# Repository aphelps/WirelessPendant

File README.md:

# WirelessPendant
Wireless Pendants

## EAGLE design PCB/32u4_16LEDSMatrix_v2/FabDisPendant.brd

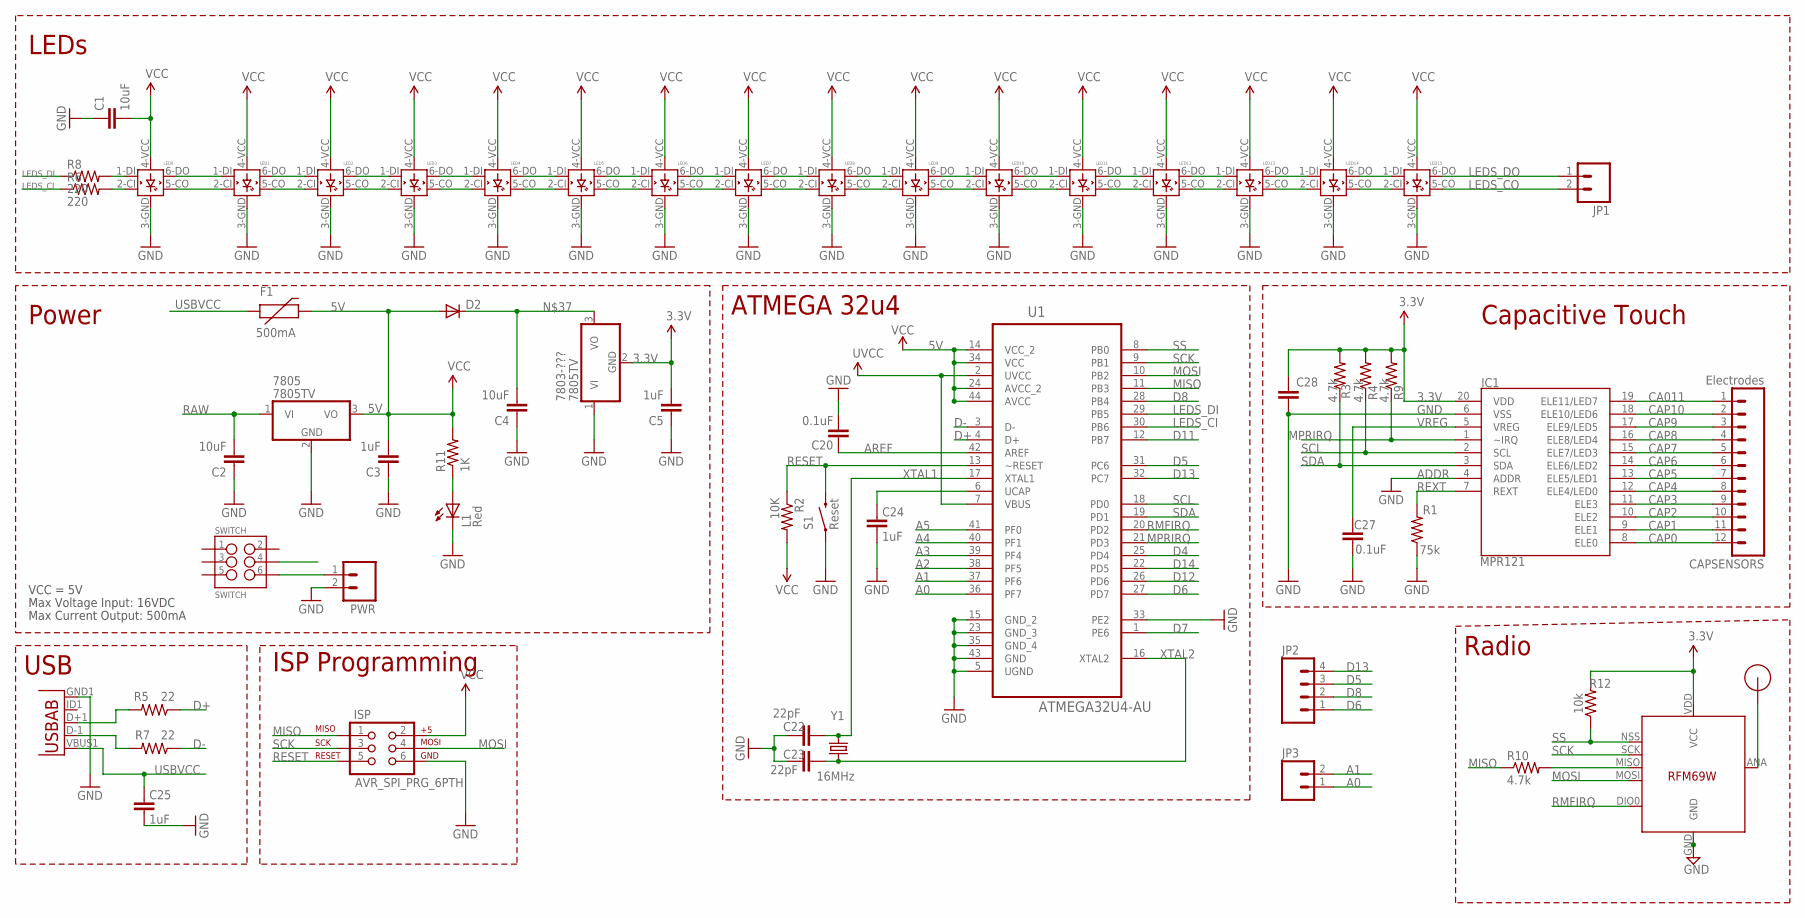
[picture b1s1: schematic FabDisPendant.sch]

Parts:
7803-???, 7805: 7805TV; TO220V
C1, C2, C4: 10uF; 1206
C3, C5: 1uF; 1206
C20, C27, C28: 0.1uF; 0603-CAP
C22, C23: 22pF; 0603-CAP
C24, C25: 1uF; 0603-CAP
CAPSENSORS: Electrodes; 1X12
D2: DIODESOD; SOD-323
F1: 500mA; PTC-1206
IC1: MPR121; QFN-20-0.4MM-V2
ISP: AVR_SPI_PRG_6PTH; 2X3
JP1, JP3: M02PTH; 1X02
JP2: M04PTH; 1X04
L1: Red; LED-0603
LED0, LED1, LED2, LED3, LED4, LED5, LED6, LED7, LED8, LED9, LED10, LED11, LED12, LED13, LED14, LED15: APA102; 5050
PWR: M025MM; SCREWTERMINAL-5MM-2
R1: 75k; 0603-RES
R2: 10K; 0603-RES
R3, R4, R9, R10: 4.7k; 0603-RES
R5, R7: 22; 0603-RES
R6, R8: 220; 0603-RES@1
R11: 1K; 0603-RES
R12: 10k; 0603-RES
RMF69: RFM69; RFM69W-MINPADS
S1: Reset; TACTILE_SWITCH_SMD
SWITCH: SWITCH; 2X3
U1: ATMEGA32U4-AU; QFP80P1200X1200X120-44N
U$1: RFM12B_ANTENNA; RFM12B-ANTENNA
X2: USB-ABIN&OUT; USB-AB-MICRO-SMD-V03-IN&OUT
Y1: 16MHz; CRYSTAL-SMD-5X3

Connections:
3.3V: 7803-???.2 (GND), C5.2, C28.1, IC1.20 (VDD), R3.2, R4.2, R9.2, R12.2, RMF69.VDD (VCC)
5V: 7805.3 (VO), C1.2, C3.2, D2.2 (A), F1.2, ISP.2, LED0.4-VCC (VCC), R2.2, R11.2, U1.14 (VCC_2), U1.24 (AVCC_2), U1.34 (VCC), U1.44 (AVCC)
.: R10.2, RMF69.MISO
A0: JP3.1, U1.36 (PF7)
A1: JP3.2, U1.37 (PF6)
A2: U1.38 (PF5)
A3: U1.39 (PF4)
A4: U1.40 (PF1)
A5: U1.41 (PF0)
ADDR: IC1.4 (ADDR)
AREF: C20.2, U1.42 (AREF)
CA011: CAPSENSORS.1, IC1.19 (ELE11/LED7)
CAP0: CAPSENSORS.12, IC1.8 (ELE0)
CAP1: CAPSENSORS.11, IC1.9 (ELE1)
CAP2: CAPSENSORS.10, IC1.10 (ELE2)
CAP3: CAPSENSORS.9, IC1.11 (ELE3)
CAP4: CAPSENSORS.8, IC1.12 (ELE4/LED0)
CAP5: CAPSENSORS.7, IC1.13 (ELE5/LED1)
CAP6: CAPSENSORS.6, IC1.14 (ELE6/LED2)
CAP7: CAPSENSORS.5, IC1.15 (ELE7/LED3)
CAP8: CAPSENSORS.4, IC1.16 (ELE8/LED4)
CAP9: CAPSENSORS.3, IC1.17 (ELE9/LED5)
CAP10: CAPSENSORS.2, IC1.18 (ELE10/LED6)
D4: U1.25 (PD4)
D5: JP2.3, U1.31 (PC6)
D6: JP2.1, U1.27 (PD7)
D7: U1.1 (PE6)
D8: JP2.2, U1.28 (PB4)
D11: U1.12 (PB7)
D12: U1.26 (PD6)
D13: JP2.4, U1.32 (PC7)
D14: U1.22 (PD5)
D+: R5.1, U1.4 (D+)
D-: R7.1, U1.3 (D-)
GND: 7803-???.1 (VI), 7805.2 (GND), C1.1, C2.1, C3.1, C4.1, C5.1, C20.1, C22.2, C23.2, C24.1, C25.1, C27.2, C28.2, IC1.6 (VSS), ISP.6, L1.C, LED0.3-GND (GND), LED1.3-GND (GND), LED2.3-GND (GND), LED3.3-GND (GND), LED4.3-GND (GND), LED5.3-GND (GND), LED6.3-GND (GND), LED7.3-GND (GND), LED8.3-GND (GND), LED9.3-GND (GND), LED10.3-GND (GND), LED11.3-GND (GND), LED12.3-GND (GND), LED13.3-GND (GND), LED14.3-GND (GND), LED15.3-GND (GND), PWR.2, R1.1, RMF69.GND, S1.1, U1.5 (UGND), U1.15 (GND_2), U1.23 (GND_3), U1.33 (PE2), U1.35 (GND_4), U1.43 (GND), X2.GND1 (GND)
LEDS_CI: R6.1, U1.30 (PB6)
LEDS_CO: JP1.2, LED15.5-CO (CO)
LEDS_DI: R8.1, U1.29 (PB5)
LEDS_DO: JP1.1, LED15.6-DO (DO)
MISO: ISP.1, R10.1, U1.11 (PB3)
MOSI: ISP.4, RMF69.MOSI, U1.10 (PB2)
MPRIRQ: IC1.1 (~IRQ), R9.1, U1.21 (PD3)
unnamed: LED0.1-DI (DI), R8.2
unnamed: LED0.6-DO (DO), LED1.1-DI (DI)
unnamed: LED0.2-CI (CI), R6.2
unnamed: LED0.5-CO (CO), LED1.2-CI (CI)
unnamed: LED1.6-DO (DO), LED2.1-DI (DI)
unnamed: LED1.5-CO (CO), LED2.2-CI (CI)
unnamed: LED2.6-DO (DO), LED3.1-DI (DI)
unnamed: LED2.5-CO (CO), LED3.2-CI (CI)
unnamed: LED3.5-CO (CO), LED4.2-CI (CI)
unnamed: LED3.6-DO (DO), LED4.1-DI (DI)
unnamed: LED4.6-DO (DO), LED5.1-DI (DI)
unnamed: LED4.5-CO (CO), LED5.2-CI (CI)
unnamed: LED5.6-DO (DO), LED6.1-DI (DI)
unnamed: LED5.5-CO (CO), LED6.2-CI (CI)
unnamed: LED6.6-DO (DO), LED7.1-DI (DI)
unnamed: LED6.5-CO (CO), LED7.2-CI (CI)
unnamed: LED7.5-CO (CO), LED8.2-CI (CI)
unnamed: LED7.6-DO (DO), LED8.1-DI (DI)
unnamed: LED8.6-DO (DO), LED9.1-DI (DI)
unnamed: R7.2, X2.D-1 (D-)
unnamed: R5.2, X2.D+1 (D+)
unnamed: LED8.5-CO (CO), LED9.2-CI (CI)
unnamed: LED9.6-DO (DO), LED10.1-DI (DI)
unnamed: LED9.5-CO (CO), LED10.2-CI (CI)
unnamed: RMF69.ANA (ANT), U$1.P$1
unnamed: LED10.6-DO (DO), LED11.1-DI (DI)
unnamed: LED10.5-CO (CO), LED11.2-CI (CI)
unnamed: LED11.6-DO (DO), LED12.1-DI (DI)
unnamed: LED11.5-CO (CO), LED12.2-CI (CI)
unnamed: LED12.6-DO (DO), LED13.1-DI (DI)
unnamed: LED12.5-CO (CO), LED13.2-CI (CI)
unnamed: LED13.6-DO (DO), LED14.1-DI (DI)
unnamed: LED13.5-CO (CO), LED14.2-CI (CI)
unnamed: LED14.6-DO (DO), LED15.1-DI (DI)
unnamed: LED14.5-CO (CO), LED15.2-CI (CI)
unnamed: PWR.1, SWITCH.6
unnamed: 7803-???.3 (VO), C4.2, D2.1 (C)
unnamed: L1.A, R11.1
unnamed: C24.2, U1.6 (UCAP)
RAW: 7805.1 (VI), C2.2, SWITCH.4
RESET: ISP.5, R2.1, S1.3 (2), U1.13 (~RESET)
REXT: IC1.7 (REXT), R1.2
RMFIRQ: RMF69.DIO0, U1.20 (PD2)
SCK: ISP.3, RMF69.SCK, U1.9 (PB1)
SCL: IC1.2 (SCL), R4.1, U1.18 (PD0)
SDA: IC1.3 (SDA), R3.1, U1.19 (PD1)
SS: R12.1, RMF69.NSS (SEL), U1.8 (PB0)
USBVCC: C25.2, F1.1, U1.2 (UVCC), U1.7 (VBUS), X2.VBUS1 (VBUS)
VCC: LED1.4-VCC (VCC), LED2.4-VCC (VCC), LED3.4-VCC (VCC), LED4.4-VCC (VCC), LED5.4-VCC (VCC), LED6.4-VCC (VCC), LED7.4-VCC (VCC), LED8.4-VCC (VCC), LED9.4-VCC (VCC), LED10.4-VCC (VCC), LED11.4-VCC (VCC), LED12.4-VCC (VCC), LED13.4-VCC (VCC), LED14.4-VCC (VCC), LED15.4-VCC (VCC)
VREG: C27.1, IC1.5 (VREG)
XTAL1: C22.1, U1.17 (XTAL1), Y1.3 (2)
XTAL2: C23.1, U1.16 (XTAL2), Y1.1

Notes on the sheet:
Max Voltage Input: 16VDC
Max Current Output: 500mA
VCC = 5V
LEDs
Power
USB
ISP Programming
Capacitive Touch
ATMEGA 32u4
Radio

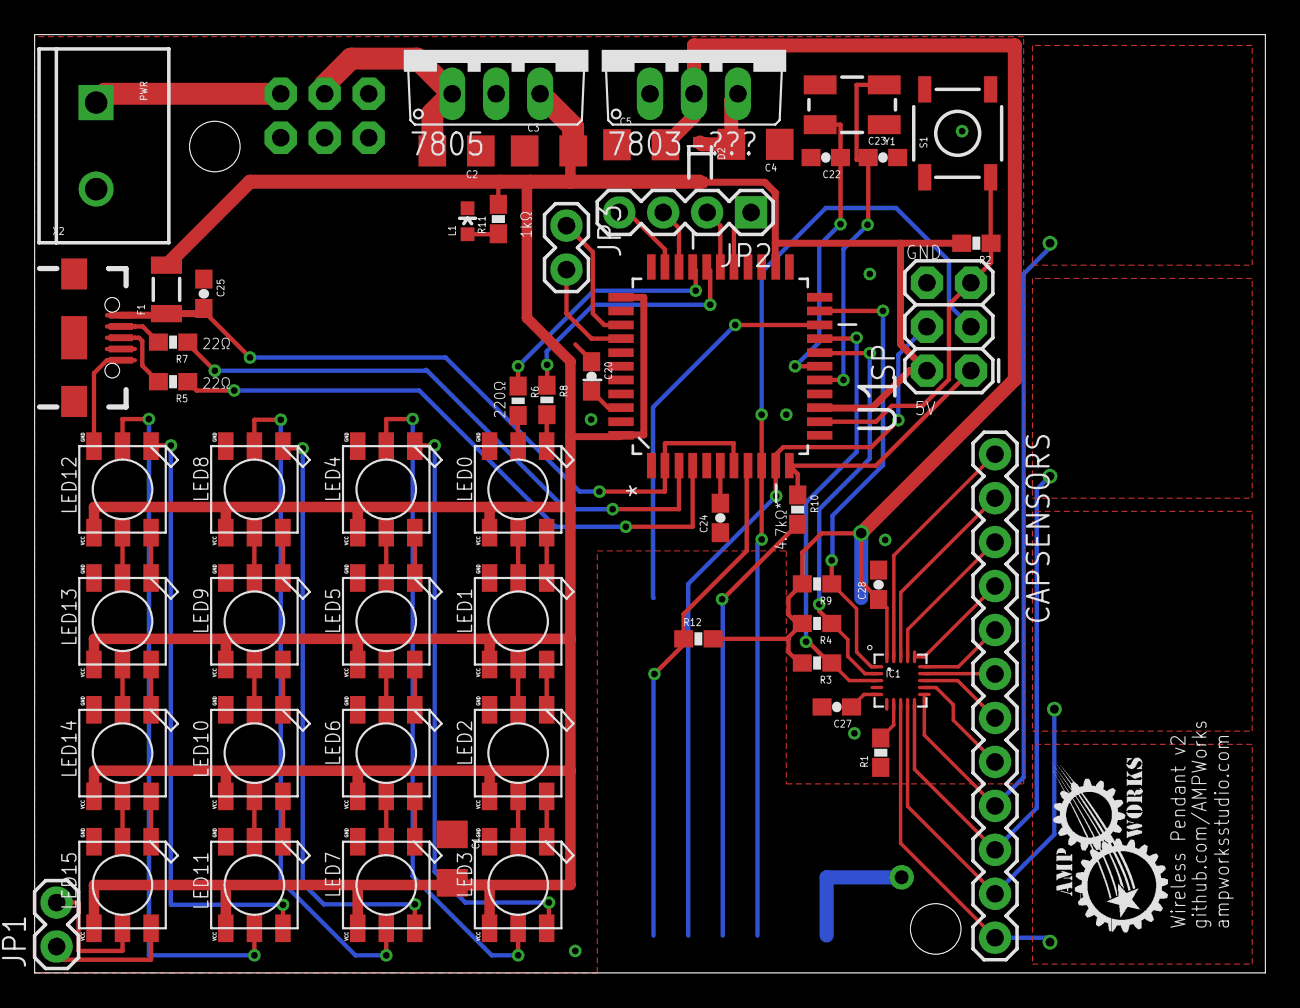
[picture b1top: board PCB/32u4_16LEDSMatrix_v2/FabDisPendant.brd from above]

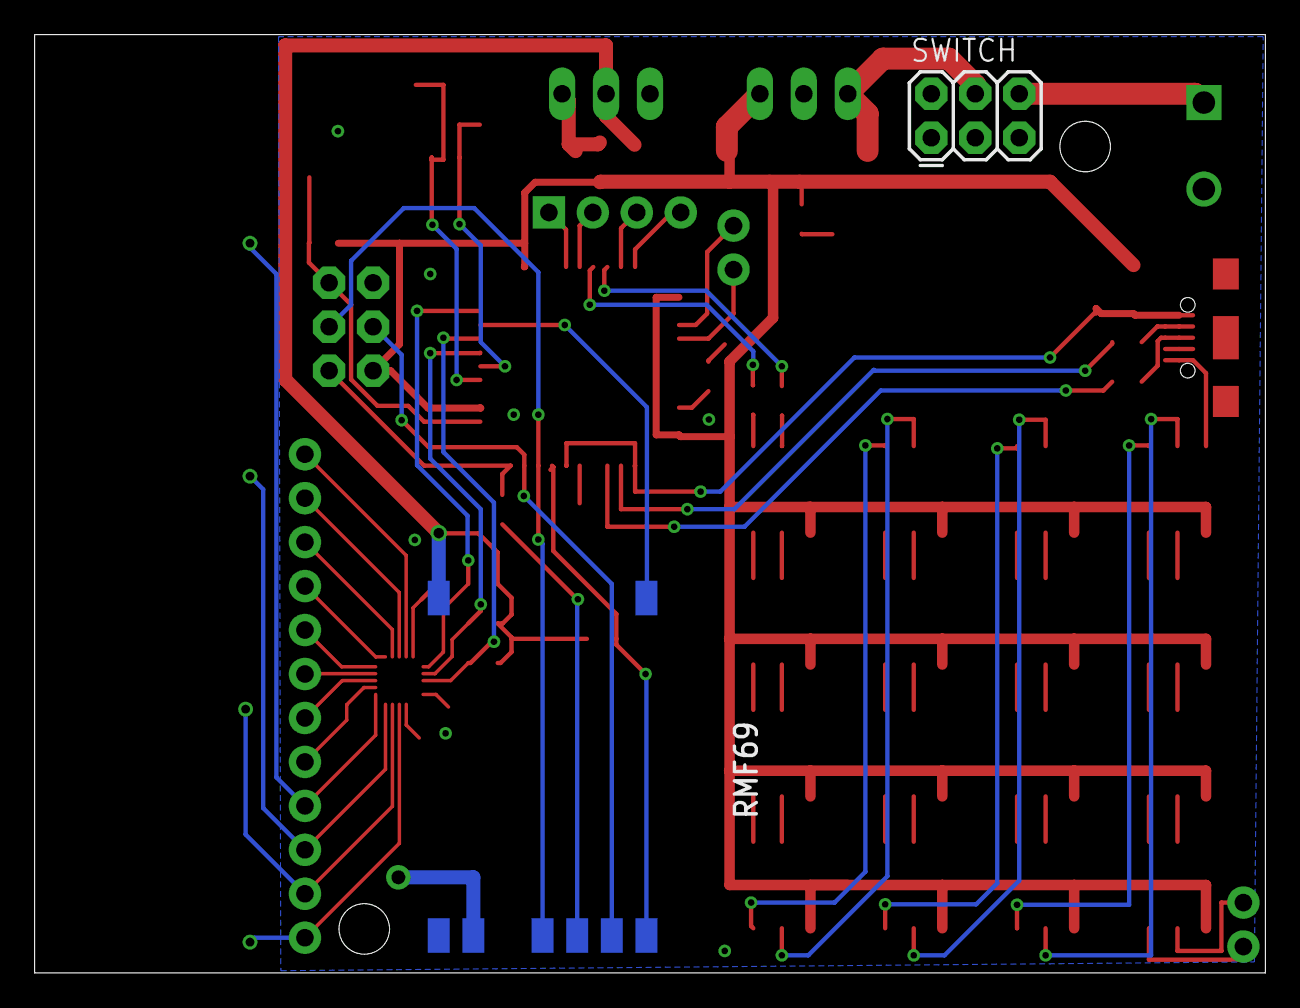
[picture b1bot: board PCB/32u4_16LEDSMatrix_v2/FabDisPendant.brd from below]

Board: 2 copper layers, 71.1 x 54.2 mm, 59 parts (2 on the bottom side), 84 nets.

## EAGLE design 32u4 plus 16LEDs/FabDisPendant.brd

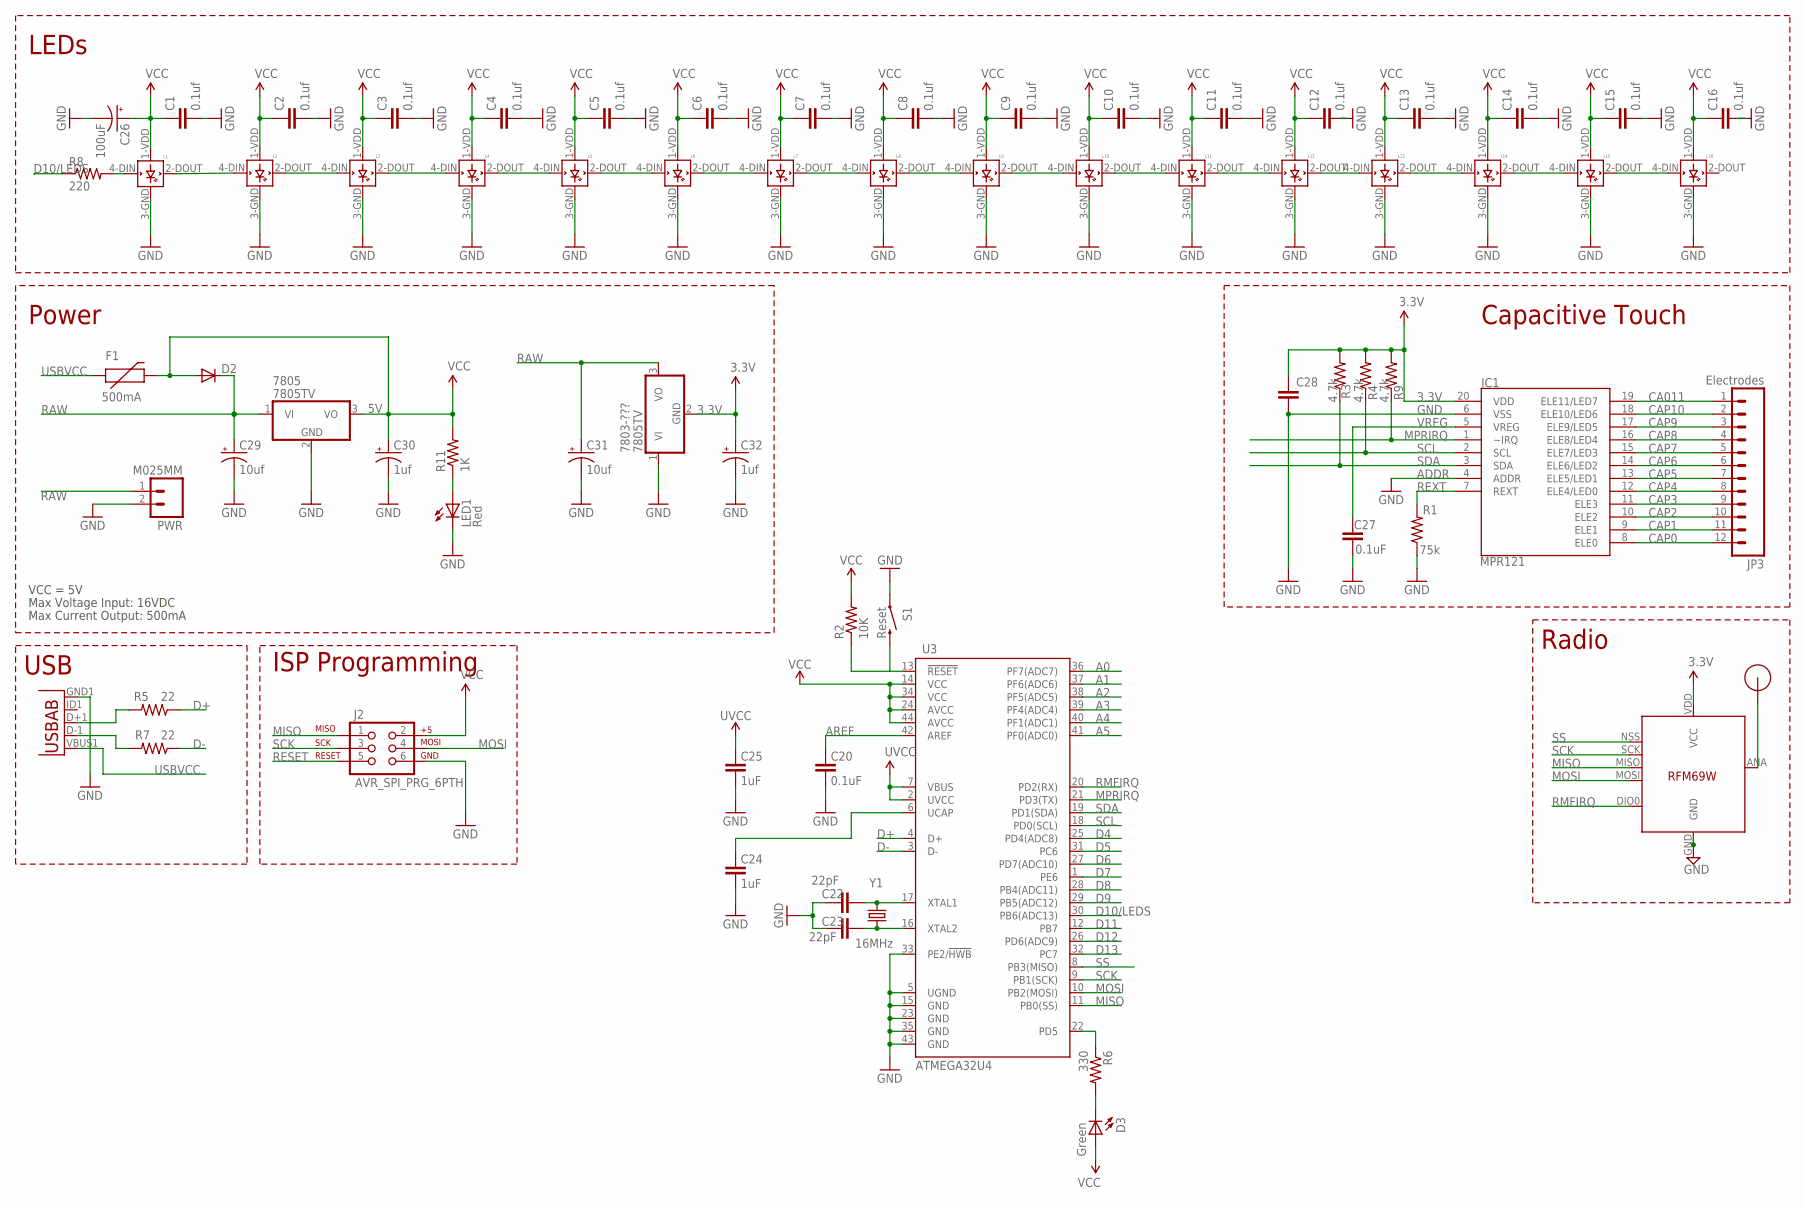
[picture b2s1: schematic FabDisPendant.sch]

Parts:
7803-???, 7805: 7805TV; TO220V
C1, C2, C3, C4, C5, C6, C7, C8, C9, C10, C11, C12, C13, C14, C15, C16: 0.1uf; 0603-CAP
C20, C27, C28: 0.1uF; 0603-CAP
C22, C23: 22pF; 0603-CAP
C24, C25: 1uF; 0603-CAP
C26: 100uF; NIC_10X10.5_CAP
C29, C31: 10uf; CPOL-RADIAL-10UF-25V
C30, C32: 1uf; CPOL-RADIAL-10UF-25V
D2: DIODESOD; SOD-323
D3: Green; LED-0603
F1: 500mA; PTC-1206
IC1: MPR121; QFN-20-0.4MM-V2
J2: AVR_SPI_PRG_6PTH; 2X3
JP3: Electrodes; 1X12
L1, L2, L3, L4, L5, L6, L7, L8, L9, L10, L11, L12, L13, L14, L15, L16: WS2812B
LED1: Red; LED-0603
PWR: M025MM; SCREWTERMINAL-5MM-2
R1: 75k; 0603-RES
R2: 10K; 0603-RES
R3, R4, R9: 4.7k; 0603-RES
R5, R7: 22; 0603-RES
R6: 330; 0603-RES
R8: 220; 0603-RES@1
R11: 1K; 0603-RES
S1: Reset; TACTILE_SWITCH_SMD
U3: ATMEGA32U4; QFN-44-NOPAD_1:1-OUTFAKES
U$1: RFM12B_ANTENNA; RFM12B-ANTENNA
U$5: RFM69; RFM69W-MINPADS
X2: USB-ABIN&OUT; USB-AB-MICRO-SMD-V03-IN&OUT
Y1: 16MHz; CRYSTAL-SMD-5X3

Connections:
3.3V: 7803-???.2 (GND), C28.1, C32.1 (+), IC1.20 (VDD), R3.2, R4.2, R9.2, U$5.VDD (VCC)
5V: 7805.3 (VO), C1.1, C2.1, C3.1, C4.1, C5.1, C6.1, C7.1, C8.1, C9.1, C10.1, C11.1, C12.1, C13.1, C14.1, C15.1, C16.1, C26.+, C30.1 (+), D2.2 (A), D3.A, F1.2, J2.2, L1.1-VDD (VDD), L2.1-VDD (VDD), L3.1-VDD (VDD), L4.1-VDD (VDD), L5.1-VDD (VDD), L6.1-VDD (VDD), L7.1-VDD (VDD), L8.1-VDD (VDD), L9.1-VDD (VDD), L10.1-VDD (VDD), L11.1-VDD (VDD), L12.1-VDD (VDD), L13.1-VDD (VDD), L14.1-VDD (VDD), L15.1-VDD (VDD), L16.1-VDD (VDD), R2.2, R11.2, U3.14 (VCC), U3.24 (AVCC), U3.34 (VCC), U3.44 (AVCC)
A0: U3.36 (PF7(ADC7))
A1: U3.37 (PF6(ADC6))
A2: U3.38 (PF5(ADC5))
A3: U3.39 (PF4(ADC4))
A4: U3.40 (PF1(ADC1))
A5: U3.41 (PF0(ADC0))
ADDR: IC1.4 (ADDR)
AREF: C20.2, U3.42 (AREF)
CA011: IC1.19 (ELE11/LED7), JP3.1
CAP0: IC1.8 (ELE0), JP3.12
CAP1: IC1.9 (ELE1), JP3.11
CAP2: IC1.10 (ELE2), JP3.10
CAP3: IC1.11 (ELE3), JP3.9
CAP4: IC1.12 (ELE4/LED0), JP3.8
CAP5: IC1.13 (ELE5/LED1), JP3.7
CAP6: IC1.14 (ELE6/LED2), JP3.6
CAP7: IC1.15 (ELE7/LED3), JP3.5
CAP8: IC1.16 (ELE8/LED4), JP3.4
CAP9: IC1.17 (ELE9/LED5), JP3.3
CAP10: IC1.18 (ELE10/LED6), JP3.2
D4: U3.25 (PD4(ADC8))
D5: U3.31 (PC6)
D6: U3.27 (PD7(ADC10))
D7: U3.1 (PE6)
D8: U3.28 (PB4(ADC11))
D9: U3.29 (PB5(ADC12))
D10/LEDS: R8.1, U3.30 (PB6(ADC13))
D11: U3.12 (PB7)
D12: U3.26 (PD6(ADC9))
D13: U3.32 (PC7)
D+: R5.1, U3.4 (D+)
D-: R7.1, U3.3 (D-)
GND: 7803-???.1 (VI), 7805.2 (GND), C1.2, C2.2, C3.2, C4.2, C5.2, C6.2, C7.2, C8.2, C9.2, C10.2, C11.2, C12.2, C13.2, C14.2, C15.2, C16.2, C20.1, C22.2, C23.2, C24.1, C25.1, C26.-, C27.2, C28.2, C29.2 (-), C30.2 (-), C31.2 (-), C32.2 (-), IC1.6 (VSS), J2.6, L1.3-GND (GND), L2.3-GND (GND), L3.3-GND (GND), L4.3-GND (GND), L5.3-GND (GND), L6.3-GND (GND), L7.3-GND (GND), L8.3-GND (GND), L9.3-GND (GND), L10.3-GND (GND), L11.3-GND (GND), L12.3-GND (GND), L13.3-GND (GND), L14.3-GND (GND), L15.3-GND (GND), L16.3-GND (GND), LED1.C, PWR.2, R1.1, S1.1, U3.5 (UGND), U3.15 (GND), U3.23 (GND), U3.33 (PE2/!HWB), U3.35 (GND), U3.43 (GND), U$5.GND, X2.GND1 (GND)
MISO: J2.1, U3.11 (PB0(SS)), U$5.MISO
MOSI: J2.4, U3.10 (PB2(MOSI)), U$5.MOSI
MPRIRQ: IC1.1 (~IRQ), R9.1, U3.21 (PD3(TX))
unnamed: L1.4-DIN (DIN), R8.2
unnamed: L1.2-DOUT (DOUT), L2.4-DIN (DIN)
unnamed: L2.2-DOUT (DOUT), L3.4-DIN (DIN)
unnamed: L3.2-DOUT (DOUT), L4.4-DIN (DIN)
unnamed: L5.2-DOUT (DOUT), L6.4-DIN (DIN)
unnamed: L6.2-DOUT (DOUT), L7.4-DIN (DIN)
unnamed: L7.2-DOUT (DOUT), L8.4-DIN (DIN)
unnamed: L9.2-DOUT (DOUT), L10.4-DIN (DIN)
unnamed: L10.2-DOUT (DOUT), L11.4-DIN (DIN)
unnamed: L11.2-DOUT (DOUT), L12.4-DIN (DIN)
unnamed: L8.2-DOUT (DOUT), L9.4-DIN (DIN)
unnamed: L4.2-DOUT (DOUT), L5.4-DIN (DIN)
unnamed: L13.2-DOUT (DOUT), L14.4-DIN (DIN)
unnamed: L14.2-DOUT (DOUT), L15.4-DIN (DIN)
unnamed: L15.2-DOUT (DOUT), L16.4-DIN (DIN)
unnamed: L12.2-DOUT (DOUT), L13.4-DIN (DIN)
unnamed: C23.1, U3.16 (XTAL2), Y1.1
unnamed: C22.1, U3.17 (XTAL1), Y1.3 (2)
unnamed: C24.2, U3.6 (UCAP)
unnamed: R7.2, X2.D-1 (D-)
unnamed: R5.2, X2.D+1 (D+)
unnamed: U$1.P$1, U$5.ANA (ANT)
unnamed: LED1.A, R11.1
unnamed: D3.C, R6.2
unnamed: R6.1, U3.22 (PD5)
RAW: 7803-???.3 (VO), 7805.1 (VI), C29.1 (+), C31.1 (+), D2.1 (C), PWR.1
RESET: J2.5, R2.1, S1.3 (2), U3.13 (!RESET)
REXT: IC1.7 (REXT), R1.2
RMFIRQ: U3.20 (PD2(RX)), U$5.DIO0
SCK: J2.3, U3.9 (PB1(SCK)), U$5.SCK
SCL: IC1.2 (SCL), R4.1, U3.18 (PD0(SCL))
SDA: IC1.3 (SDA), R3.1, U3.19 (PD1(SDA))
SS: U3.8 (PB3(MISO)), U$5.NSS (SEL)
USBVCC: C25.2, F1.1, U3.2 (UVCC), U3.7 (VBUS), X2.VBUS1 (VBUS)
VREG: C27.1, IC1.5 (VREG)

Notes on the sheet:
Max Voltage Input: 16VDC
Max Current Output: 500mA
VCC = 5V
LEDs
Power
USB
ISP Programming
Radio
Capacitive Touch

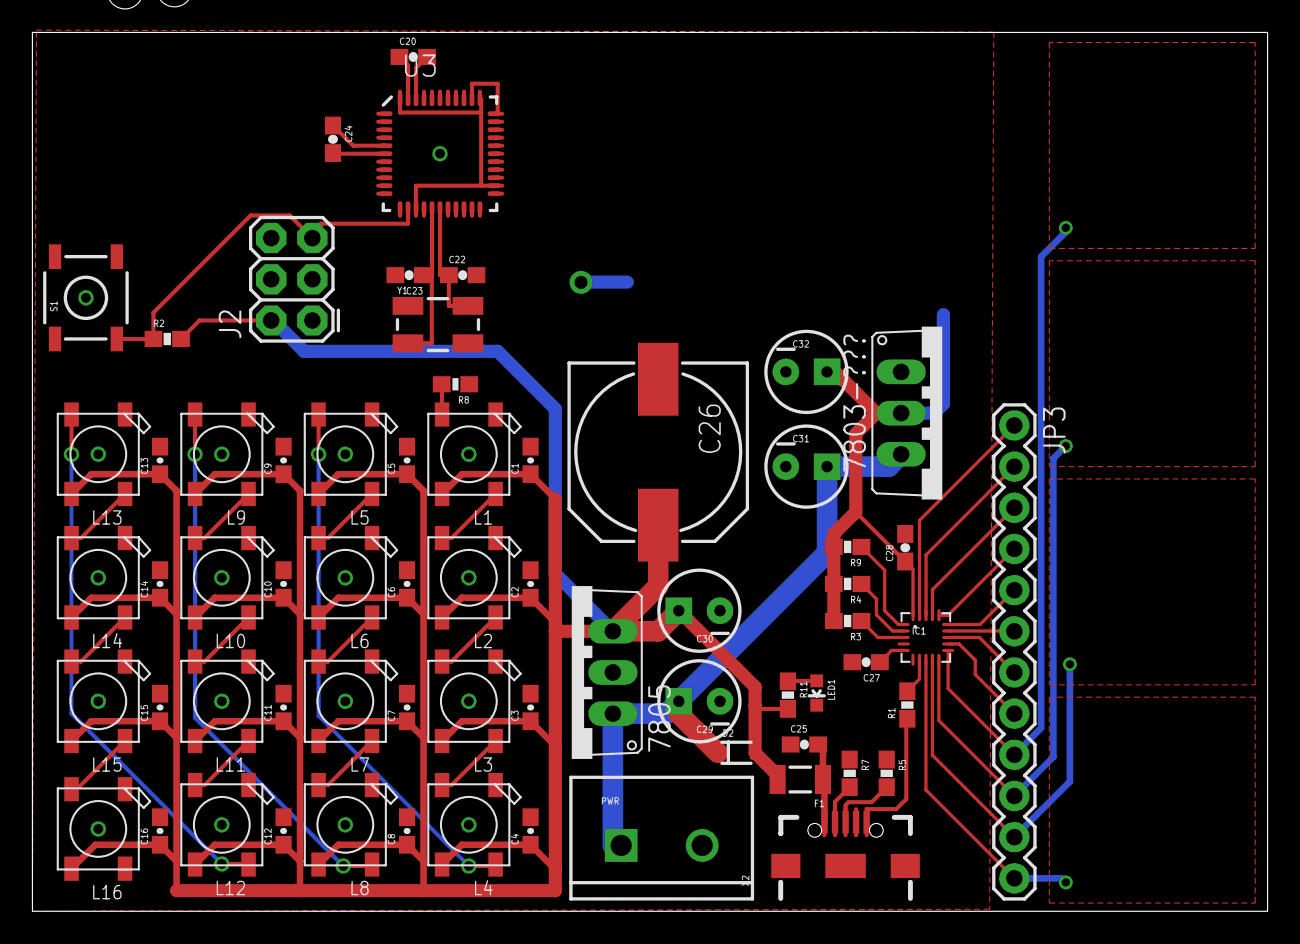
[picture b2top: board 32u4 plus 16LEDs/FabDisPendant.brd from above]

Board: 2 copper layers, 76.2 x 54.2 mm, 68 parts (1 on the bottom side), 55 nets.

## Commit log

2016-01-07 Initial commit of FabDIs pendant work
2016-01-07 Routed MPR121 and USB
2016-01-07 Initial ATMega32u4 based pendant
2016-01-07 Switch to 7805 regulator
2016-01-07 Initial autoroute
2016-01-07 Substantial rearrangement
2016-01-07 Checkin prior to autorouting
2016-01-07 Autorouted and DRC'd. 1st version sent to PCB
2016-01-07 Further rearangement
2016-01-07 More improvements, checkin before rearrangement
2016-01-10 Restructured to add code
2016-01-14 Continued improvement on the board design
2016-01-14 Added initial bringup and pendant code
2016-01-22 Switched from the TQDN package to an AU package
2016-01-22 Renamed directory
2016-01-23 Completed switch to using 32u4 with the AU package
2016-02-22 Added RS485 to the prototype's configuration
2016-02-22 Implemented use of ProgramHandler and MessageHandler
2016-02-22 Converted to using TimeSync for timers
2016-02-29 Added platformio build for 32u4 based boards
2016-02-29 Added initial startup commands
2016-04-21 Second revision of wireless pendant
2016-04-21 Finished PCB v2 basics
2016-04-21 Added headers for some digital and analog pins
2016-04-26 FInished up changes to the board

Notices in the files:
parts and their libraries:
SparkFun-Capacitors: Licensing: Creative Commons ShareAlike 4.0 International - https://creativecommons.org/licenses/by-sa/4.0
